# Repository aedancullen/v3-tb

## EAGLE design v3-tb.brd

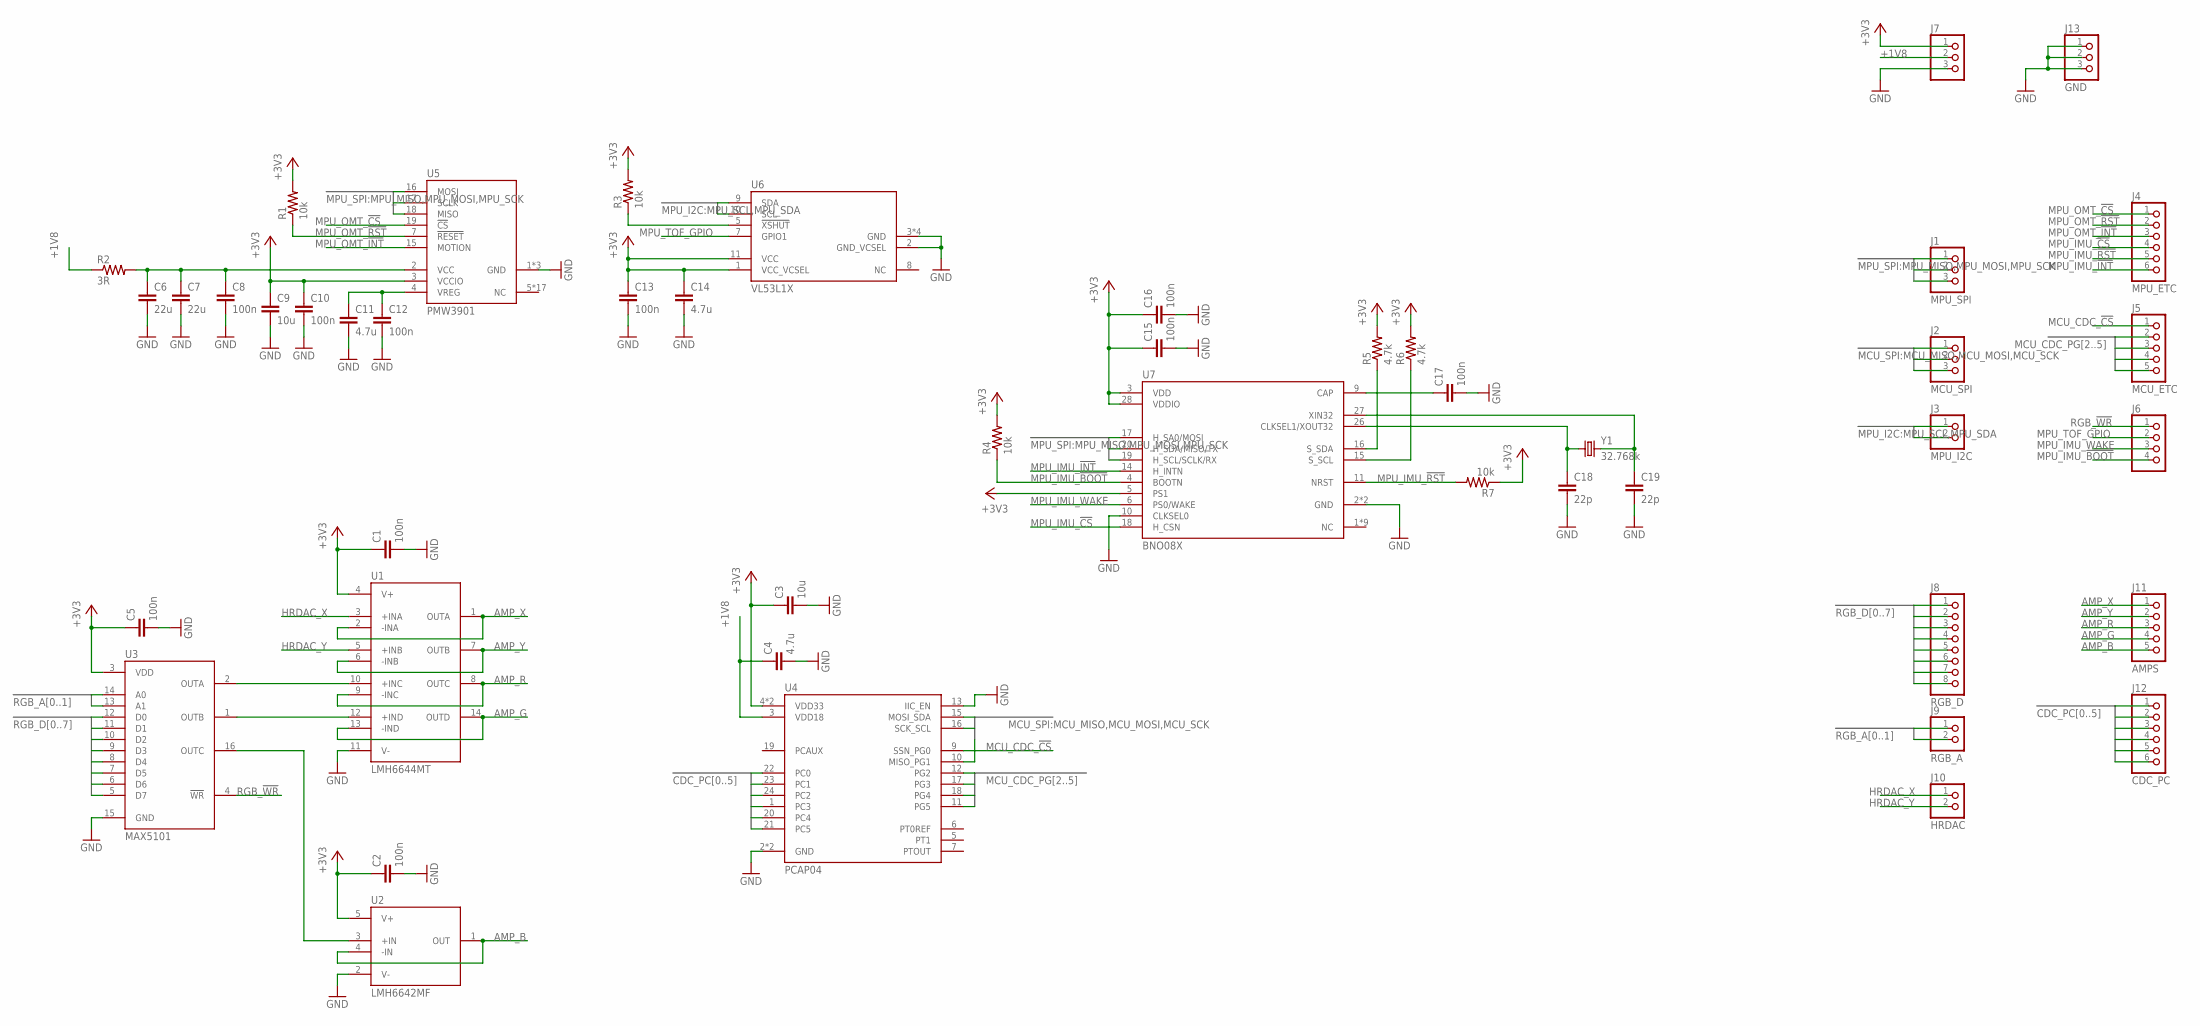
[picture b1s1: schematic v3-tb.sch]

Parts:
C1, C2, C5, C8, C10, C12, C13, C15, C16, C17: 100n; C0603
C3, C9: 10u; C0603
C4, C11, C14: 4.7u; C0603
C6, C7: 22u; C0603
C18, C19: 22p; C0603
J1: MPU_SPI; 1X03
J2: MCU_SPI; 1X03
J3: MPU_I2C; 1X02
J4: MPU_ETC; 1X06
J5: MCU_ETC; 1X05
J6: PINHD-1X4; 1X04
J7: PINHD-1X3; 1X03
J8: RGB_D; 1X08
J9: RGB_A; 1X02
J10: HRDAC; 1X02
J11: AMPS; 1X05
J12: CDC_PC; 1X06
J13: GND; 1X03
R1, R3, R4, R7: 10k; R0603
R2: 3R; R0603
R5, R6: 4.7k; R0603
U1: LMH6644MT; SOP65P640X120-14N
U2: LMH6642MF; SOT95P280X145-5N
U3: MAX5101; SOP65P640X110-16N
U4: PCAP04; QFN50P400X400X100-24N
U5: PMW3901
U6: VL53L1X
U7: BNO08X
Y1: 32.768k; FC-12M

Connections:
+1V8: C4.1, J7.2, R2.1, U4.3 (VDD18)
+3V3: C1.1, C2.1, C3.1, C5.1, C9.1, C10.1, C13.1, C14.1, C15.1, C16.1, J7.1, R1.2, R3.2, R4.2, R5.2, R6.2, R7.1, U1.4 (V+), U2.5 (V+), U3.3 (VDD), U4.4 (VDD33), U4.14 (VDD33), U5.3 (VCCIO), U6.1 (VCC_VCSEL), U6.11 (VCC), U7.3 (VDD), U7.5 (PS1), U7.28 (VDDIO)
AMP_B: J11.5, U2.1 (OUT), U2.4 (-IN)
AMP_G: J11.4, U1.13 (-IND), U1.14 (OUTD)
AMP_R: J11.3, U1.8 (OUTC), U1.9 (-INC)
AMP_X: J11.1, U1.1 (OUTA), U1.2 (-INA)
AMP_Y: J11.2, U1.6 (-INB), U1.7 (OUTB)
CDC_PC0: J12.3, U4.22 (PC0)
CDC_PC1: J12.4, U4.23 (PC1)
CDC_PC2: J12.5, U4.24 (PC2)
CDC_PC3: J12.6, U4.1 (PC3)
CDC_PC4: J12.1, U4.20 (PC4)
CDC_PC5: J12.2, U4.21 (PC5)
GND: C1.2, C2.2, C3.2, C4.2, C5.2, C6.2, C7.2, C8.2, C9.2, C10.2, C11.2, C12.2, C13.2, C14.2, C15.2, C16.2, C17.2, C18.2, C19.2, J7.3, J13.1, J13.2, J13.3, U1.11 (V-), U2.2 (V-), U3.15 (GND), U4.2 (GND), U4.8 (GND), U4.13 (IIC_EN), U5.1 (GND), U5.21 (GND), U5.29 (GND), U6.2 (GND_VCSEL), U6.3 (GND), U6.4 (GND), U6.6 (GND), U6.12 (GND), U7.2 (GND), U7.10 (CLKSEL0), U7.25 (GND)
HRDAC_X: J10.1, U1.3 (+INA)
HRDAC_Y: J10.2, U1.5 (+INB)
MCU_CDC_!CS: J5.1, U4.9 (SSN_PG0)
MCU_CDC_PG2: J5.2, U4.12 (PG2)
MCU_CDC_PG3: J5.3, U4.17 (PG3)
MCU_CDC_PG4: J5.4, U4.18 (PG4)
MCU_CDC_PG5: J5.5, U4.11 (PG5)
MCU_MISO: J2.2, U4.10 (MISO_PG1)
MCU_MOSI: J2.1, U4.15 (MOSI_SDA)
MCU_SCK: J2.3, U4.16 (SCK_SCL)
MPU_IMU_!BOOT: J6.4, R4.1, U7.4 (BOOTN)
MPU_IMU_!CS: J4.4, U7.18 (H_CSN)
MPU_IMU_!INT: J4.6, U7.14 (H_INTN)
MPU_IMU_!RST: J4.5, R7.2, U7.11 (NRST)
MPU_IMU_WAKE: J6.3, U7.6 (PS0/WAKE)
MPU_MISO: J1.2, U5.18 (MISO), U7.20 (H_SDA/MISO/TX)
MPU_MOSI: J1.1, U5.16 (MOSI), U7.17 (H_SA0/MOSI)
MPU_OMT_!CS: J4.1, U5.19 (!CS)
MPU_OMT_!INT: J4.3, U5.15 (MOTION)
MPU_OMT_!RST: J4.2, R1.1, U5.7 (!RESET)
MPU_SCK: J1.3, U5.17 (SCLK), U7.19 (H_SCL/SCLK/RX)
MPU_SCL: J3.2, U6.10 (SCL)
MPU_SDA: J3.1, U6.9 (SDA)
MPU_TOF_GPIO: J6.2, U6.7 (GPIO1)
unnamed: C11.1, C12.1, U5.4 (VREG)
unnamed: R6.1, U7.15 (S_SCL)
unnamed: C6.1, C7.1, C8.1, R2.2, U5.2 (VCC)
unnamed: R3.1, U6.5 (!XSHUT)
unnamed: C19.1, U7.27 (XIN32), Y1.2
unnamed: U1.10 (+INC), U3.2 (OUTA)
unnamed: U1.12 (+IND), U3.1 (OUTB)
unnamed: U2.3 (+IN), U3.16 (OUTC)
unnamed: R5.1, U7.16 (S_SDA)
unnamed: C17.1, U7.9 (CAP)
unnamed: C18.1, U7.26 (CLKSEL1/XOUT32), Y1.1
RGB_!WR: J6.1, U3.4 (!WR)
RGB_A0: J9.1, U3.14 (A0)
RGB_A1: J9.2, U3.13 (A1)
RGB_D0: J8.1, U3.12 (D0)
RGB_D1: J8.2, U3.11 (D1)
RGB_D2: J8.3, U3.10 (D2)
RGB_D3: J8.4, U3.9 (D3)
RGB_D4: J8.5, U3.8 (D4)
RGB_D5: J8.6, U3.7 (D5)
RGB_D6: J8.7, U3.6 (D6)
RGB_D7: J8.8, U3.5 (D7)

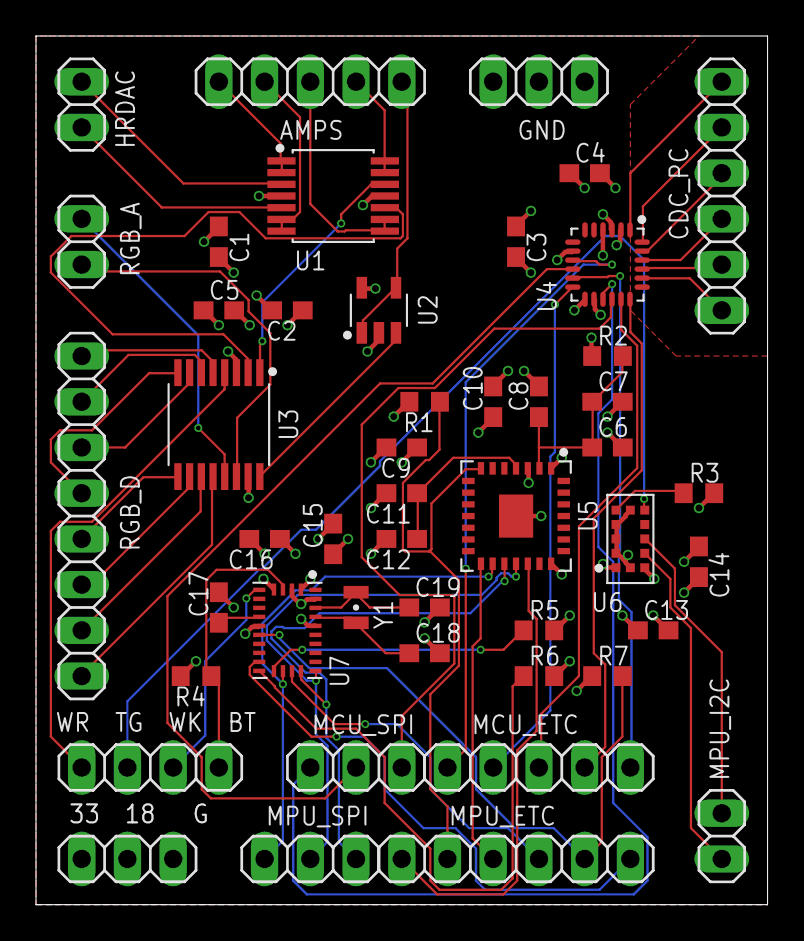
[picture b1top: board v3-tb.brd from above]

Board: 4 copper layers, 40.6 x 48.3 mm, 47 parts (0 on the bottom side), 60 nets.

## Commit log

2019-10-06 Initial V3-TB rev.A schematic
2019-10-06 BNO08X stuff
2019-10-07 Adding headers
2019-10-07 Finish headers
2019-10-07 Update headers
2019-10-07 Add WAKE pin on IMU
2019-10-07 Add board
2019-10-07 Route as 4layer
2019-10-08 Add text
2019-10-09 Add polygon fills
2019-10-09 Tent vias
2019-10-09 Fix text

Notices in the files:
v3-tb.brd:
(C) 2019 PVE
